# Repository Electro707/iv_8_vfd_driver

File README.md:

# Dual IV-8 VFD Display Drivers

This project is to drive two IV-8 displays

# History

This project started because I scored two IV-8 VFD Displays off a flea market, and thus I needed something to drive them

# Project Structure
- CAD: FreeCAD source files for the enclosure (WIP)
- PCB_Driver: KiCAD files for the driver board
- PCB_IV-8: KiCAD files for the IV-8 mounting board
- PCB_IV-8_Test: KiCAD files for a test board equivalent to above, used before using a real display in case the circuit is borked
- Sim_Osci: KiCAD files for a simulation of the oscillating circuit, taken from an EEVBlog forum
- Firmware_count: A simple firmware that counts the VFDs up from 0 to 99
- Firmware_main1: The primary firmware, this one also implements UART communication with a host

# Driver Board Issue, Rev 1
There were some erratas that proped out during testing of Rev 1 of the driver board. The following hardware bug fixes must be made for the board to be usable
- For the filament drive circuit, R17 needs to be shorted, and add two series 25ohm resistor (by cutting traces) of `FIL_A` and `FIL_B`
- Add a series 100kohm resistor between the Q1-Q3 and the outputs of Q6 to the gate of the PFET
    - Turns out there was a maximum Source-to-Gate limit of +-20v, which this circuit clearly exceeds when driving the FETs. With the 100k resistor, when driving the segment Vgs is at -5.83v

# License
This project is licensed under GPLv3. See [LICENSE.md](LICENSE.md) for details.

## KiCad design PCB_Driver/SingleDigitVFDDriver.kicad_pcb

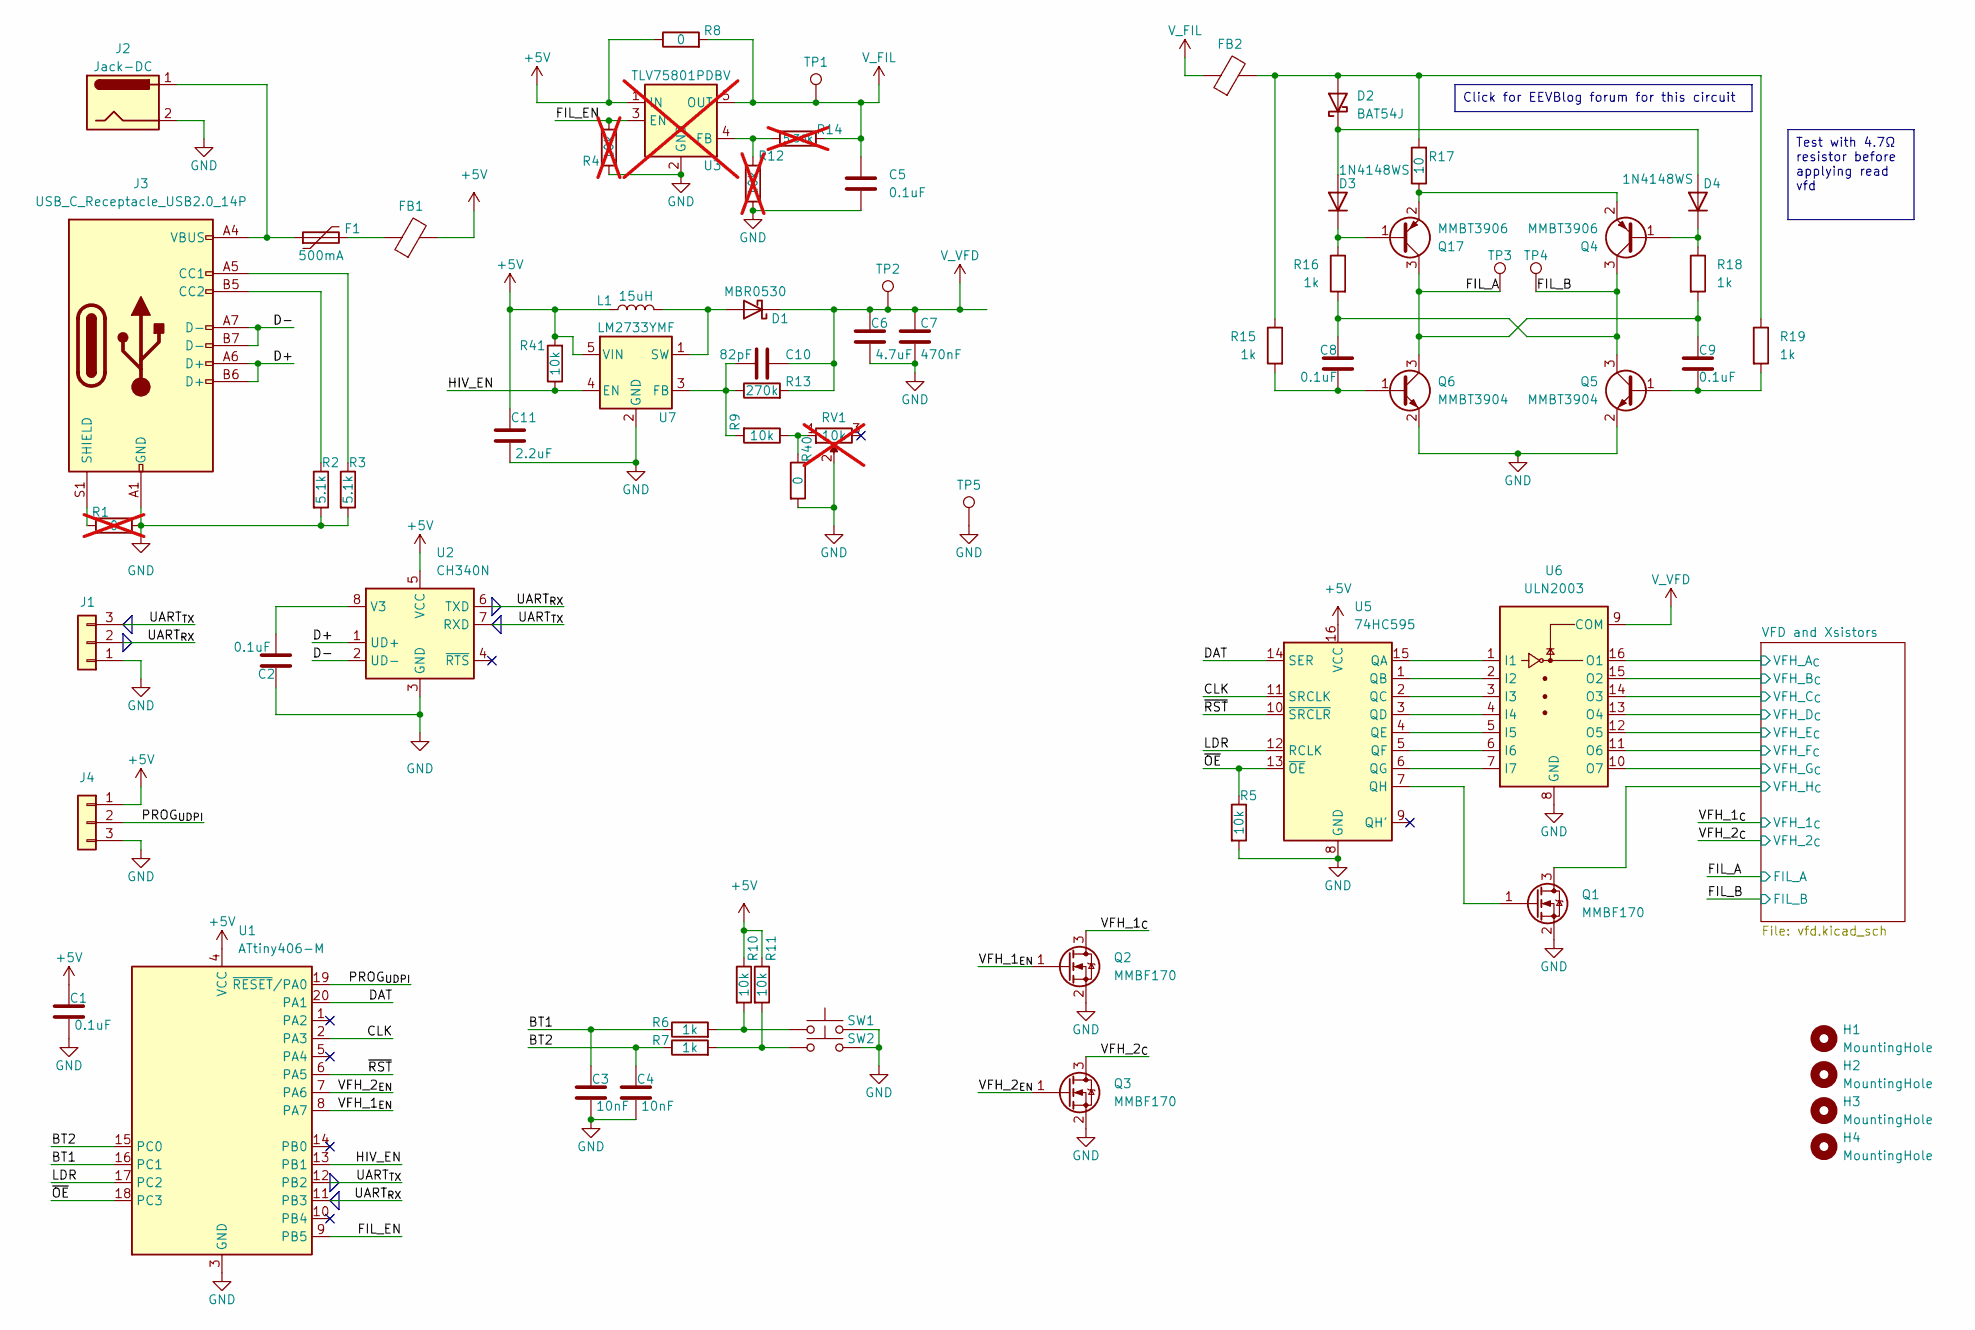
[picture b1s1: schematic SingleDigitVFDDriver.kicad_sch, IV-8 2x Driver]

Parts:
C1, C2, C5, C8, C9: 0.1uF; C_0805_2012Metric
C3, C4: 10nF; C_0805_2012Metric
C6: 4.7uF; C_1206_3216Metric
C7: 470nF; C_0805_2012Metric
C10: 82pF; C_0805_2012Metric
C11: 2.2uF; C_0805_2012Metric
D1: MBR0530; D_SOD-123
D2: BAT54J; D_SOD-323F
D3, D4: 1N4148WS; D_SOD-323
F1: 500mA; Fuse_1206_3216Metric
FB1, FB2: FerriteBead; L_0805_2012Metric
H1, H2, H3, H4: MountingHole; MountingHole_3.2mm_M3_DIN965
J1: Conn_01x03; PinSocket_1x03_P2.54mm_Vertical
J2: Jack-DC; BarrelJack_Horizontal
J3: USB_C_Receptacle_USB2.0_14P; USB_C_Receptacle_GCT_USB4085
J4: Conn_01x03; PinHeader_1x03_P2.54mm_Vertical
L1: 15uH; L_1210_3225Metric
Q1, Q2, Q3: MMBF170; SOT-23
Q4, Q17: MMBT3906; SOT-23
Q5, Q6: MMBT3904; SOT-23
R1: 0; R_0805_2012Metric; not fitted
R2, R3: 5.1k; R_0805_2012Metric
R4, R12: 10k; R_0805_2012Metric; not fitted
R5, R9, R10, R11, R41: 10k; R_0805_2012Metric
R6, R7, R15, R16, R18, R19: 1k; R_0805_2012Metric
R8, R40: 0; R_0805_2012Metric
R13: 270k; R_0805_2012Metric
R14: 5.36k; R_0805_2012Metric; not fitted
R17: 10; R_0805_2012Metric
RV1: 10k; Potentiometer_Bourns_3266W_Vertical; not fitted
SW1, SW2: SW_Push; SW_PUSH_6mm
TP1, TP2, TP3, TP4, TP5: TestPoint; TestPoint_Keystone_5005-5009_Compact
U1: ATtiny406-M; VQFN-20-1EP_3x3mm_P0.4mm_EP1.7x1.7mm
U2: CH340N; SOP-8_3.9x4.9mm_P1.27mm
U3: TLV75801PDBV; SOT-23-5; not fitted
U5: 74HC595; SOIC-16_3.9x9.9mm_P1.27mm
U6: ULN2003; SOIC-16_3.9x9.9mm_P1.27mm
U7: LM2733YMF; SOT-23-5

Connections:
+5V: C1.1, C11.1, FB1.2, J4.1, L1.1, R8.1, R10.1, R11.1, R41.2, U1.4 (VCC), U2.5 (VCC), U3.1 (IN), U5.16 (VCC), U7.5 (VIN)
/BT1: C3.1, R6.1, U1.16 (PC1)
/BT2: C4.1, R7.1, U1.15 (PC0)
/CLK: U1.2 (PA3), U5.11 (SRCLK)
/D+: J3.A6 (D+), J3.B6 (D+), U2.1 (UD+)
/D-: J3.A7 (D-), J3.B7 (D-), U2.2 (UD-)
/DAT: U1.20 (PA1), U5.14 (SER)
/FIL_A: C9.1, Q6.3 (C), Q17.3 (C), R18.2, TP3.1; also elsewhere on the board
/FIL_B: C8.1, Q4.3 (C), Q5.3 (C), R16.2, TP4.1; also elsewhere on the board
/FIL_EN: R4.2, U1.9 (PB5), U3.3 (EN)
/HIV_EN: R41.1, U1.13 (PB1), U7.4 (EN)
/LDR: U1.17 (PC2), U5.12 (RCLK)
/PROG_{UDPI}: J4.2, U1.19 (~RESET/PA0)
/UART_{RX}: J1.2, U1.11 (PB3), U2.6 (TXD)
/UART_{TX}: J1.3, U1.12 (PB2), U2.7 (RXD)
/VFD and Xsistors/VFH_A_{C}: U6.16 (O1); also elsewhere on the board
/VFD and Xsistors/VFH_B_{C}: U6.15 (O2); also elsewhere on the board
/VFD and Xsistors/VFH_C_{C}: U6.14 (O3); also elsewhere on the board
/VFD and Xsistors/VFH_D_{C}: U6.13 (O4); also elsewhere on the board
/VFD and Xsistors/VFH_E_{C}: U6.12 (O5); also elsewhere on the board
/VFD and Xsistors/VFH_F_{C}: U6.11 (O6); also elsewhere on the board
/VFD and Xsistors/VFH_G_{C}: U6.10 (O7); also elsewhere on the board
/VFD and Xsistors/VFH_H_{C}: Q1.3 (D); also elsewhere on the board
/VFH_1_{C}: Q2.3 (D); also elsewhere on the board
/VFH_1_{EN}: Q2.1 (G), U1.8 (PA7)
/VFH_2_{C}: Q3.3 (D); also elsewhere on the board
/VFH_2_{EN}: Q3.1 (G), U1.7 (PA6)
/~OE: R5.1, U1.18 (PC3), U5.13 (~OE)
/~RST: U1.6 (PA5), U5.10 (~SRCLR)
GND: C1.2, C2.1, C3.2, C4.2, C5.2, C6.2, C7.2, C11.2, J1.1, J2.2, J3.A1 (GND), J3.A12 (GND), J3.B1 (GND), J3.B12 (GND), J4.3, Q1.2 (S), Q2.2 (S), Q3.2 (S), Q5.2 (E), Q6.2 (E), R1.2, R2.2, R3.2, R4.1, R5.2, R12.1, R40.2, RV1.2, SW1.2, SW2.2, TP5.1, U1.3 (GND), U1.21 (GND), U2.3 (GND), U3.2 (GND), U5.8 (GND), U6.8 (GND), U7.2 (GND); also elsewhere on the board
unnamed: D1.2 (A), L1.2, U7.1 (SW)
unnamed: D2.2 (A), FB2.2, R15.1, R17.2, R19.1
unnamed: D2.1 (K), D3.2 (A), D4.2 (A)
unnamed: D3.1 (K), Q17.1 (B), R16.1
unnamed: D4.1 (K), Q4.1 (B), R18.1
unnamed: F1.1, J2.1, J3.A4 (VBUS), J3.A9 (VBUS), J3.B4 (VBUS), J3.B9 (VBUS)
unnamed: F1.2, FB1.1
unnamed: J3.A5 (CC1), R3.1
unnamed: J3.B5 (CC2), R2.1
unnamed: J3.S1 (SHIELD), R1.1
unnamed: Q1.1 (G), U5.7 (QH)
unnamed: C9.2, Q5.1 (B), R19.2
unnamed: C8.2, Q6.1 (B), R15.2
unnamed: Q4.2 (E), Q17.2 (E), R17.1
unnamed: R6.2, R10.2, SW1.1
unnamed: R7.2, R11.2, SW2.1
unnamed: R9.1, R40.1, RV1.1
unnamed: C2.2, U2.8 (V3)
unnamed: R12.2, R14.1, U3.4 (FB)
unnamed: U5.15 (QA), U6.1 (I1)
unnamed: U5.1 (QB), U6.2 (I2)
unnamed: U5.2 (QC), U6.3 (I3)
unnamed: U5.3 (QD), U6.4 (I4)
unnamed: U5.4 (QE), U6.5 (I5)
unnamed: U5.5 (QF), U6.6 (I6)
unnamed: U5.6 (QG), U6.7 (I7)
unnamed: C10.1, R9.2, R13.1, U7.3 (FB)
V_FIL: C5.1, FB2.1, R8.2, R14.2, TP1.1, U3.5 (OUT)
V_VFD: C6.1, C7.1, C10.2, D1.1 (K), R13.2, TP2.1, U6.9 (COM); also elsewhere on the board

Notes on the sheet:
Click for EEVBlog forum for this circuit
Test with 4.7Ω resistor before applying read vfd

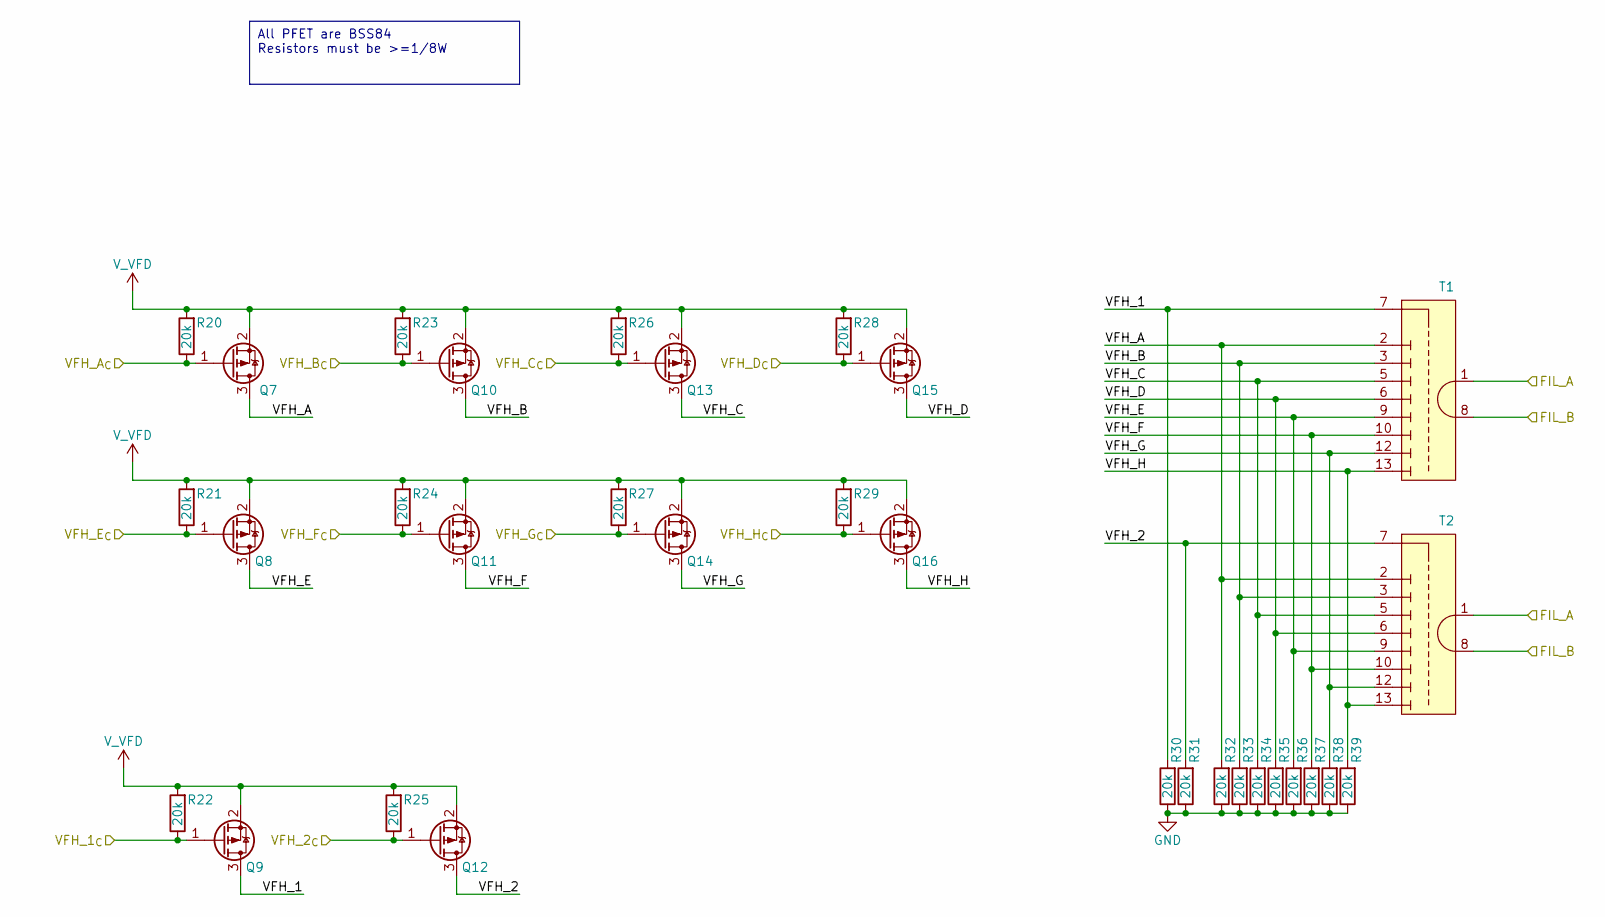
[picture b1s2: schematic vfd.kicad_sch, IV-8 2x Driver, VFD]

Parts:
Q7, Q8, Q9, Q10, Q11, Q12, Q13, Q14, Q15, Q16: BSS84; SOT-23
R20, R21, R22, R23, R24, R25, R26, R27, R28, R29, R30, R31, R32, R33, R34, R35, R36, R37, R38, R39: 20k; R_0805_2012Metric
T1, T2: IV-8 Adapter

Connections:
/FIL_A: T1.1, T2.1; also elsewhere on the board
/FIL_B: T1.8, T2.8; also elsewhere on the board
/VFD and Xsistors/VFH_1: Q9.3 (D), R30.2, T1.7
/VFD and Xsistors/VFH_2: Q12.3 (D), R31.2, T2.7
/VFD and Xsistors/VFH_A: Q7.3 (D), R32.2, T1.2, T2.2
/VFD and Xsistors/VFH_A_{C}: Q7.1 (G), R20.1; also elsewhere on the board
/VFD and Xsistors/VFH_B: Q10.3 (D), R33.2, T1.3, T2.3
/VFD and Xsistors/VFH_B_{C}: Q10.1 (G), R23.1; also elsewhere on the board
/VFD and Xsistors/VFH_C: Q13.3 (D), R34.2, T1.5, T2.5
/VFD and Xsistors/VFH_C_{C}: Q13.1 (G), R26.1; also elsewhere on the board
/VFD and Xsistors/VFH_D: Q15.3 (D), R35.2, T1.6, T2.6
/VFD and Xsistors/VFH_D_{C}: Q15.1 (G), R28.1; also elsewhere on the board
/VFD and Xsistors/VFH_E: Q8.3 (D), R36.2, T1.9, T2.9
/VFD and Xsistors/VFH_E_{C}: Q8.1 (G), R21.1; also elsewhere on the board
/VFD and Xsistors/VFH_F: Q11.3 (D), R37.2, T1.10, T2.10
/VFD and Xsistors/VFH_F_{C}: Q11.1 (G), R24.1; also elsewhere on the board
/VFD and Xsistors/VFH_G: Q14.3 (D), R38.2, T1.12, T2.12
/VFD and Xsistors/VFH_G_{C}: Q14.1 (G), R27.1; also elsewhere on the board
/VFD and Xsistors/VFH_H: Q16.3 (D), R39.2, T1.13, T2.13
/VFD and Xsistors/VFH_H_{C}: Q16.1 (G), R29.1; also elsewhere on the board
/VFH_1_{C}: Q9.1 (G), R22.1; also elsewhere on the board
/VFH_2_{C}: Q12.1 (G), R25.1; also elsewhere on the board
GND: R30.1, R31.1, R32.1, R33.1, R34.1, R35.1, R36.1, R37.1, R38.1, R39.1; also elsewhere on the board
V_VFD: Q7.2 (S), Q8.2 (S), Q9.2 (S), Q10.2 (S), Q11.2 (S), Q12.2 (S), Q13.2 (S), Q14.2 (S), Q15.2 (S), Q16.2 (S), R20.2, R21.2, R22.2, R23.2, R24.2, R25.2, R26.2, R27.2, R28.2, R29.2; also elsewhere on the board

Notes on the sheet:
All PFET are BSS84 Resistors must be >=1/8W

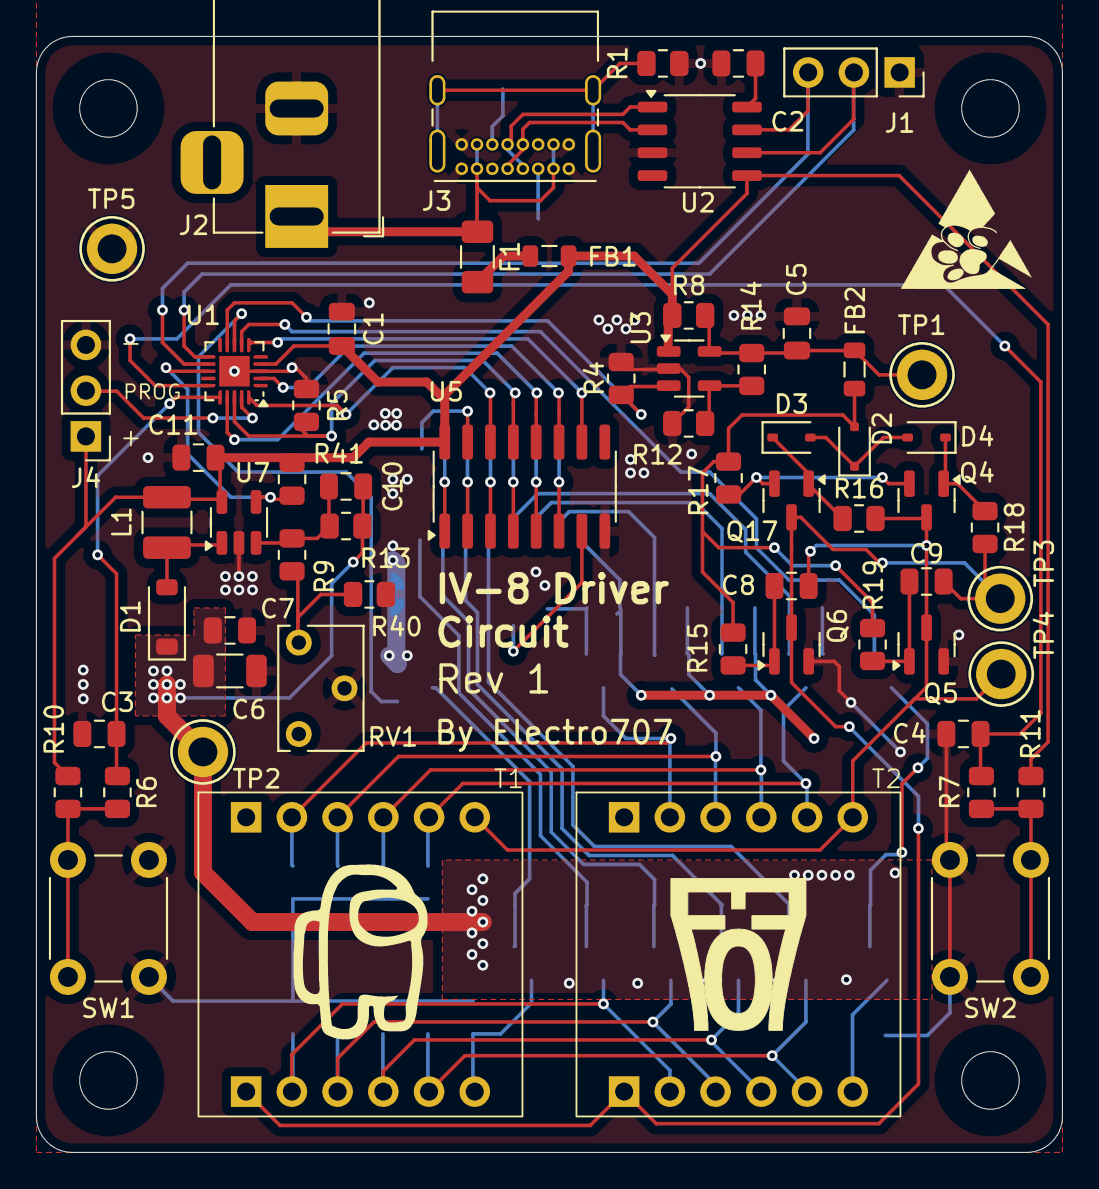
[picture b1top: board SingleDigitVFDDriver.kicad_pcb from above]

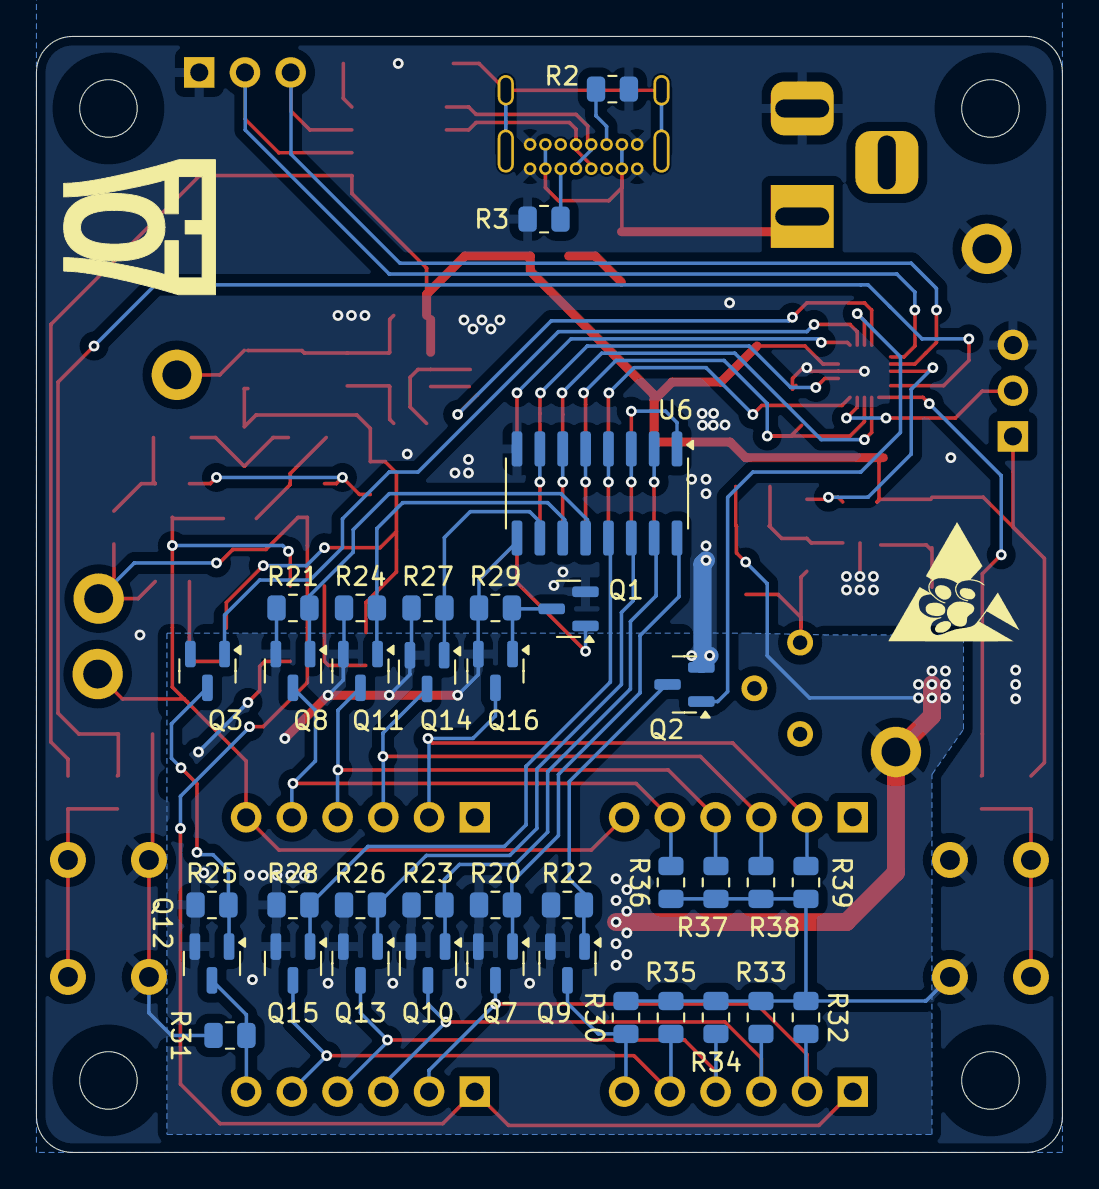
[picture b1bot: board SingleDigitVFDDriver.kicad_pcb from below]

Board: 2 copper layers, 57.0 x 62.0 mm, 101 parts (36 on the bottom side), 69 nets.

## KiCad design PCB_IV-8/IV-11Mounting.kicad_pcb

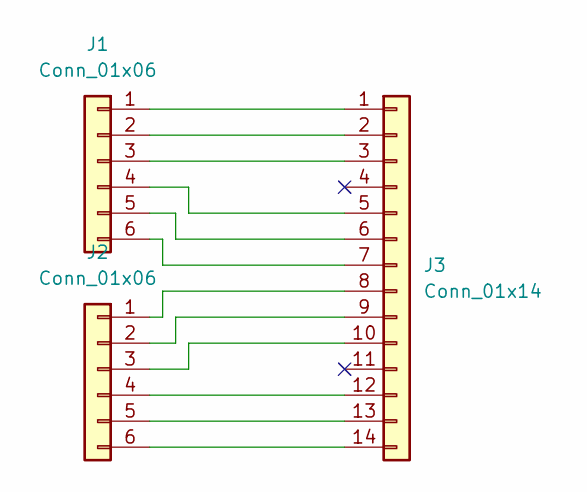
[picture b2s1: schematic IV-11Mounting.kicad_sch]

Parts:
J1, J2: Conn_01x06; PinHeader_1x06_P2.54mm_Vertical
J3: Conn_01x14; IV-8 VFD

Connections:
unnamed: J1.1, J3.1
unnamed: J1.2, J3.2
unnamed: J1.3, J3.3
unnamed: J1.4, J3.5
unnamed: J1.5, J3.6
unnamed: J1.6, J3.7
unnamed: J2.1, J3.8
unnamed: J2.2, J3.9
unnamed: J2.3, J3.10
unnamed: J2.4, J3.12
unnamed: J2.5, J3.13
unnamed: J2.6, J3.14

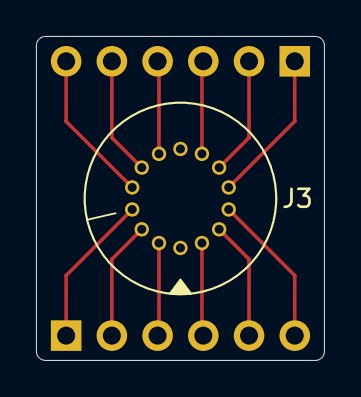
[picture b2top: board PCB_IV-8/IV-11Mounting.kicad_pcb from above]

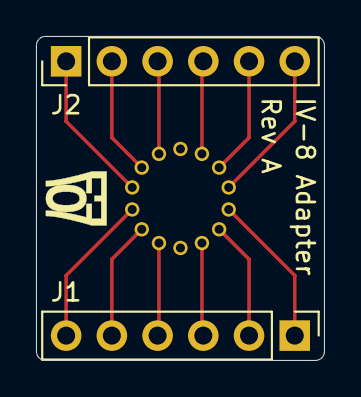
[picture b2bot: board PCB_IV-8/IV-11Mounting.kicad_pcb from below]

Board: 2 copper layers, 16.0 x 18.0 mm, 3 parts (2 on the bottom side), 12 nets.

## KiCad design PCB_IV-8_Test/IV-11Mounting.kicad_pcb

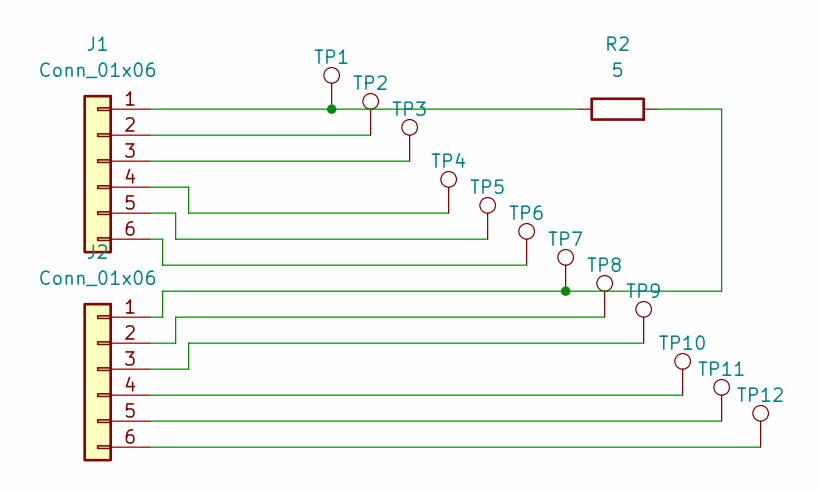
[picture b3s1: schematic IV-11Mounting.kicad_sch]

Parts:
J1, J2: Conn_01x06; PinHeader_1x06_P2.54mm_Vertical
R2: 5; R_0805_2012Metric_Pad1.20x1.40mm_HandSolder
TP1, TP2, TP3, TP4, TP5, TP6, TP7, TP8, TP9, TP10, TP11, TP12: TestPoint; TestPoint_Pad_1.5x1.5mm

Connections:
unnamed: J1.1, R2.1, TP1.1
unnamed: J1.2, TP2.1
unnamed: J1.3, TP3.1
unnamed: J1.4, TP4.1
unnamed: J1.5, TP5.1
unnamed: J1.6, TP6.1
unnamed: J2.1, R2.2, TP7.1
unnamed: J2.2, TP8.1
unnamed: J2.3, TP9.1
unnamed: J2.4, TP10.1
unnamed: J2.5, TP11.1
unnamed: J2.6, TP12.1

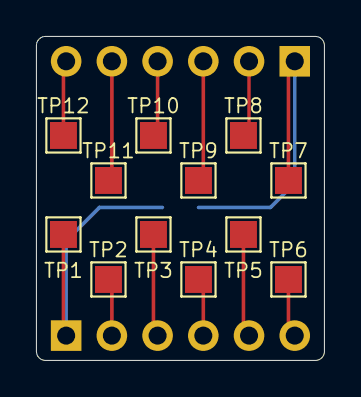
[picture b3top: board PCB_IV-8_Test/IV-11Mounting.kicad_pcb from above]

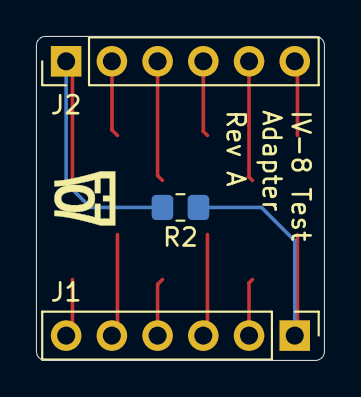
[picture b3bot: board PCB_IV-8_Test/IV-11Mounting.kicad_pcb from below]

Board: 2 copper layers, 16.0 x 18.0 mm, 15 parts (3 on the bottom side), 12 nets.

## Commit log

2024-12-22 README change
2024-12-23 Started work on enclosure. Created new firmware that isn't just a counter:
2024-12-25 Added top enclosure
